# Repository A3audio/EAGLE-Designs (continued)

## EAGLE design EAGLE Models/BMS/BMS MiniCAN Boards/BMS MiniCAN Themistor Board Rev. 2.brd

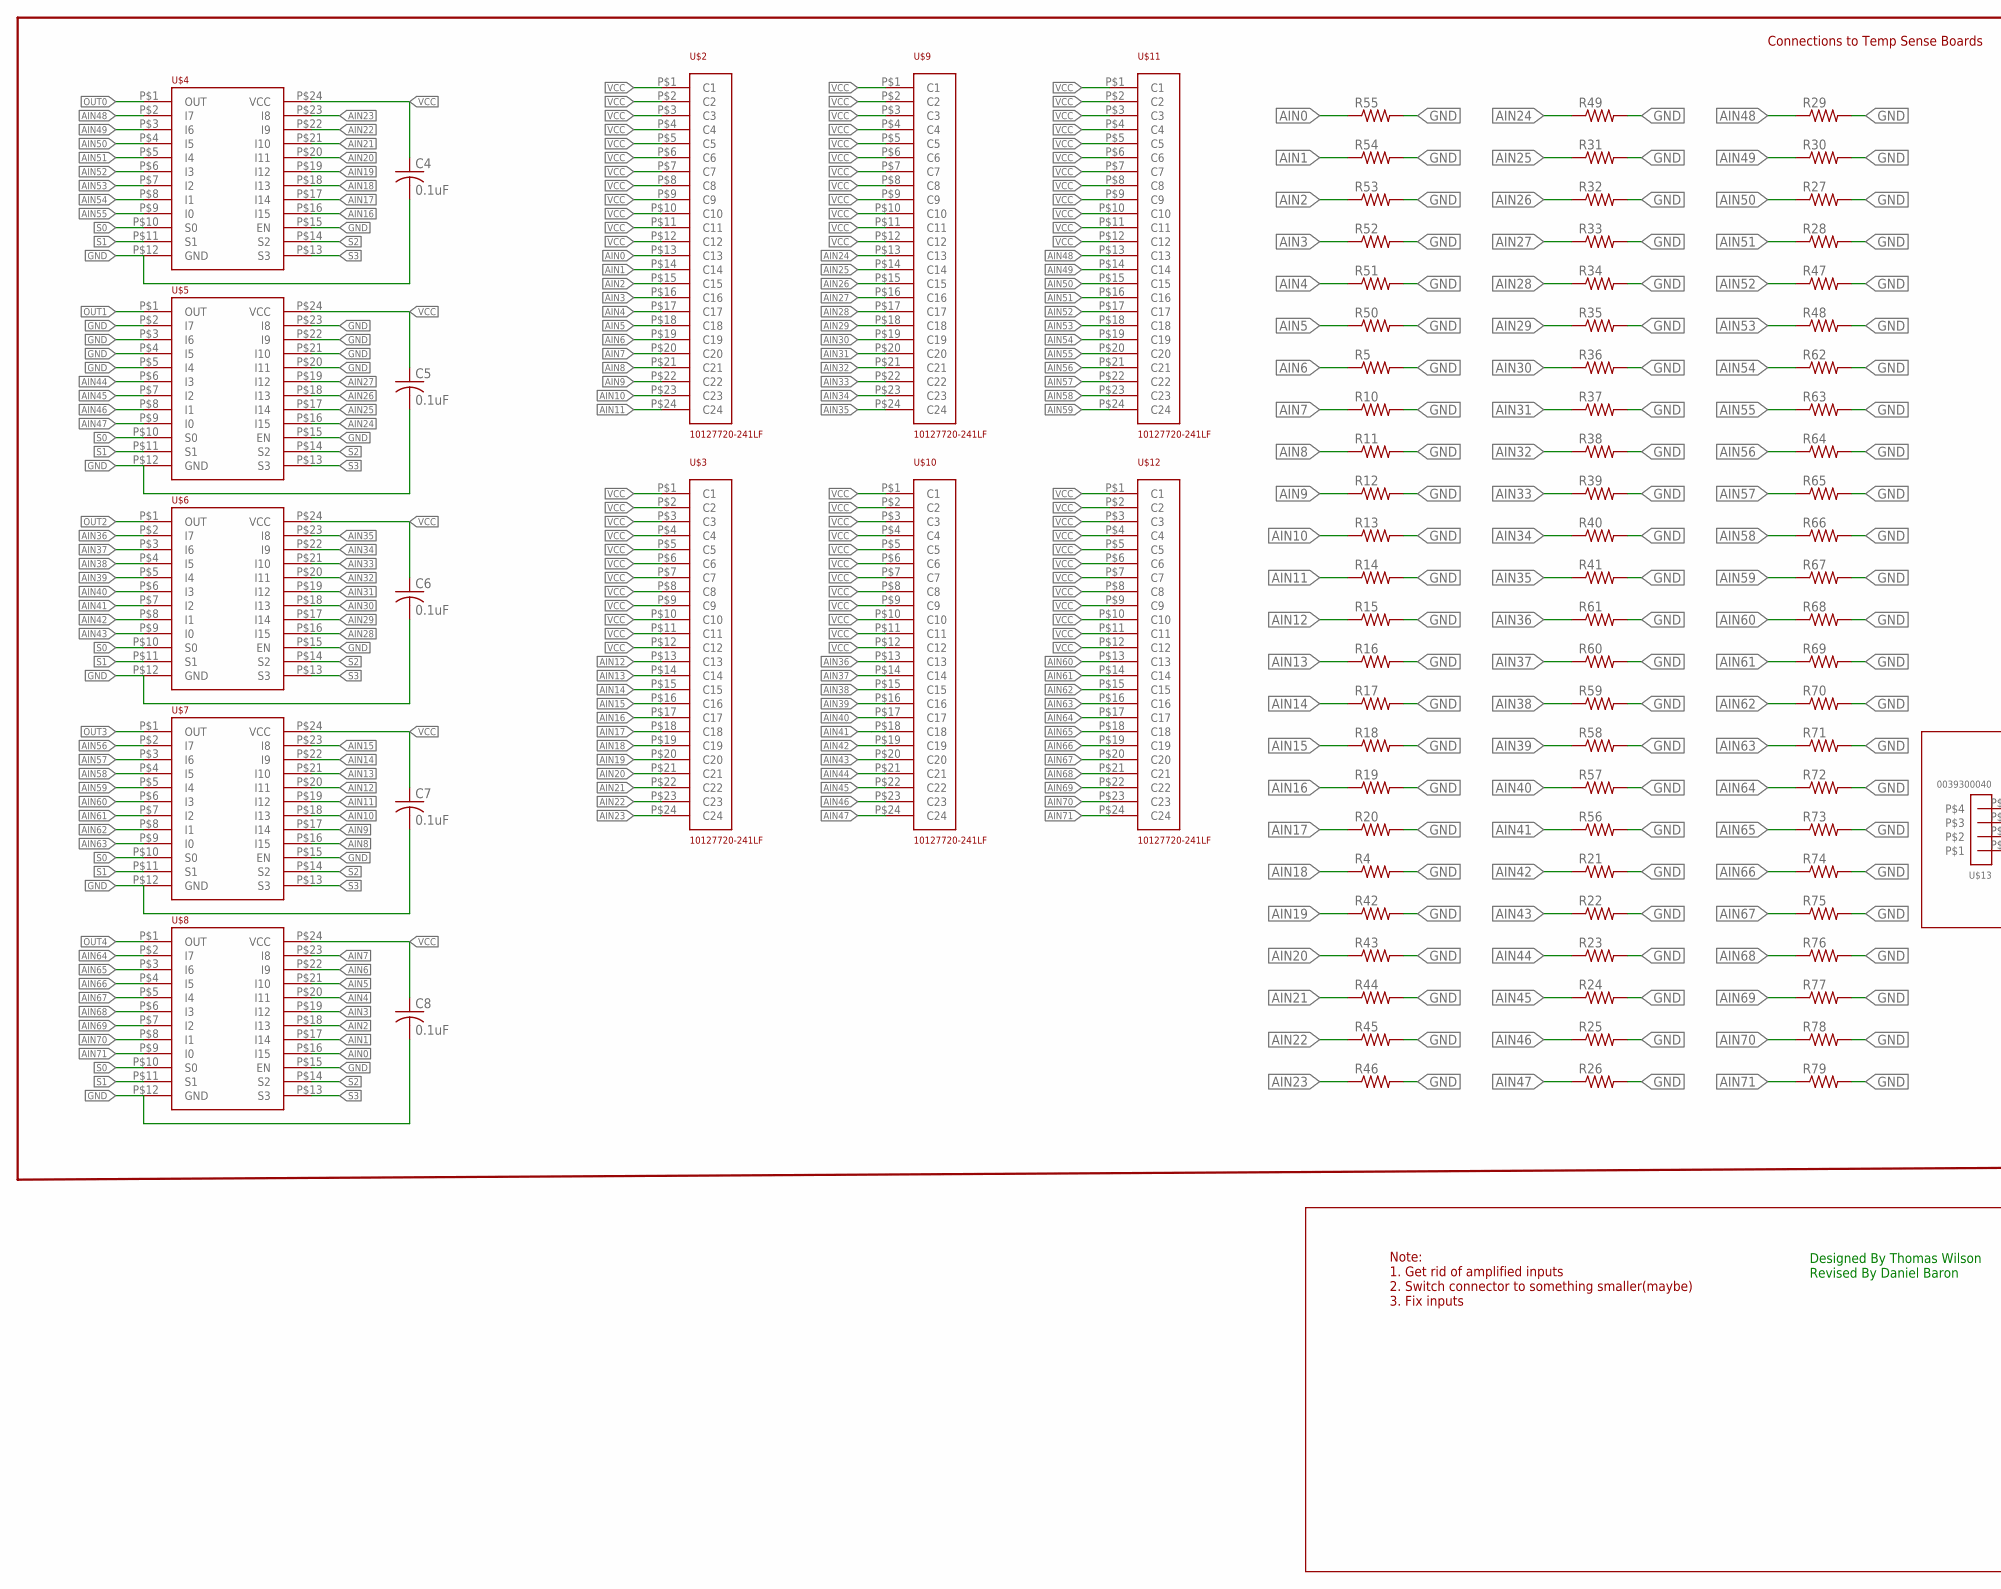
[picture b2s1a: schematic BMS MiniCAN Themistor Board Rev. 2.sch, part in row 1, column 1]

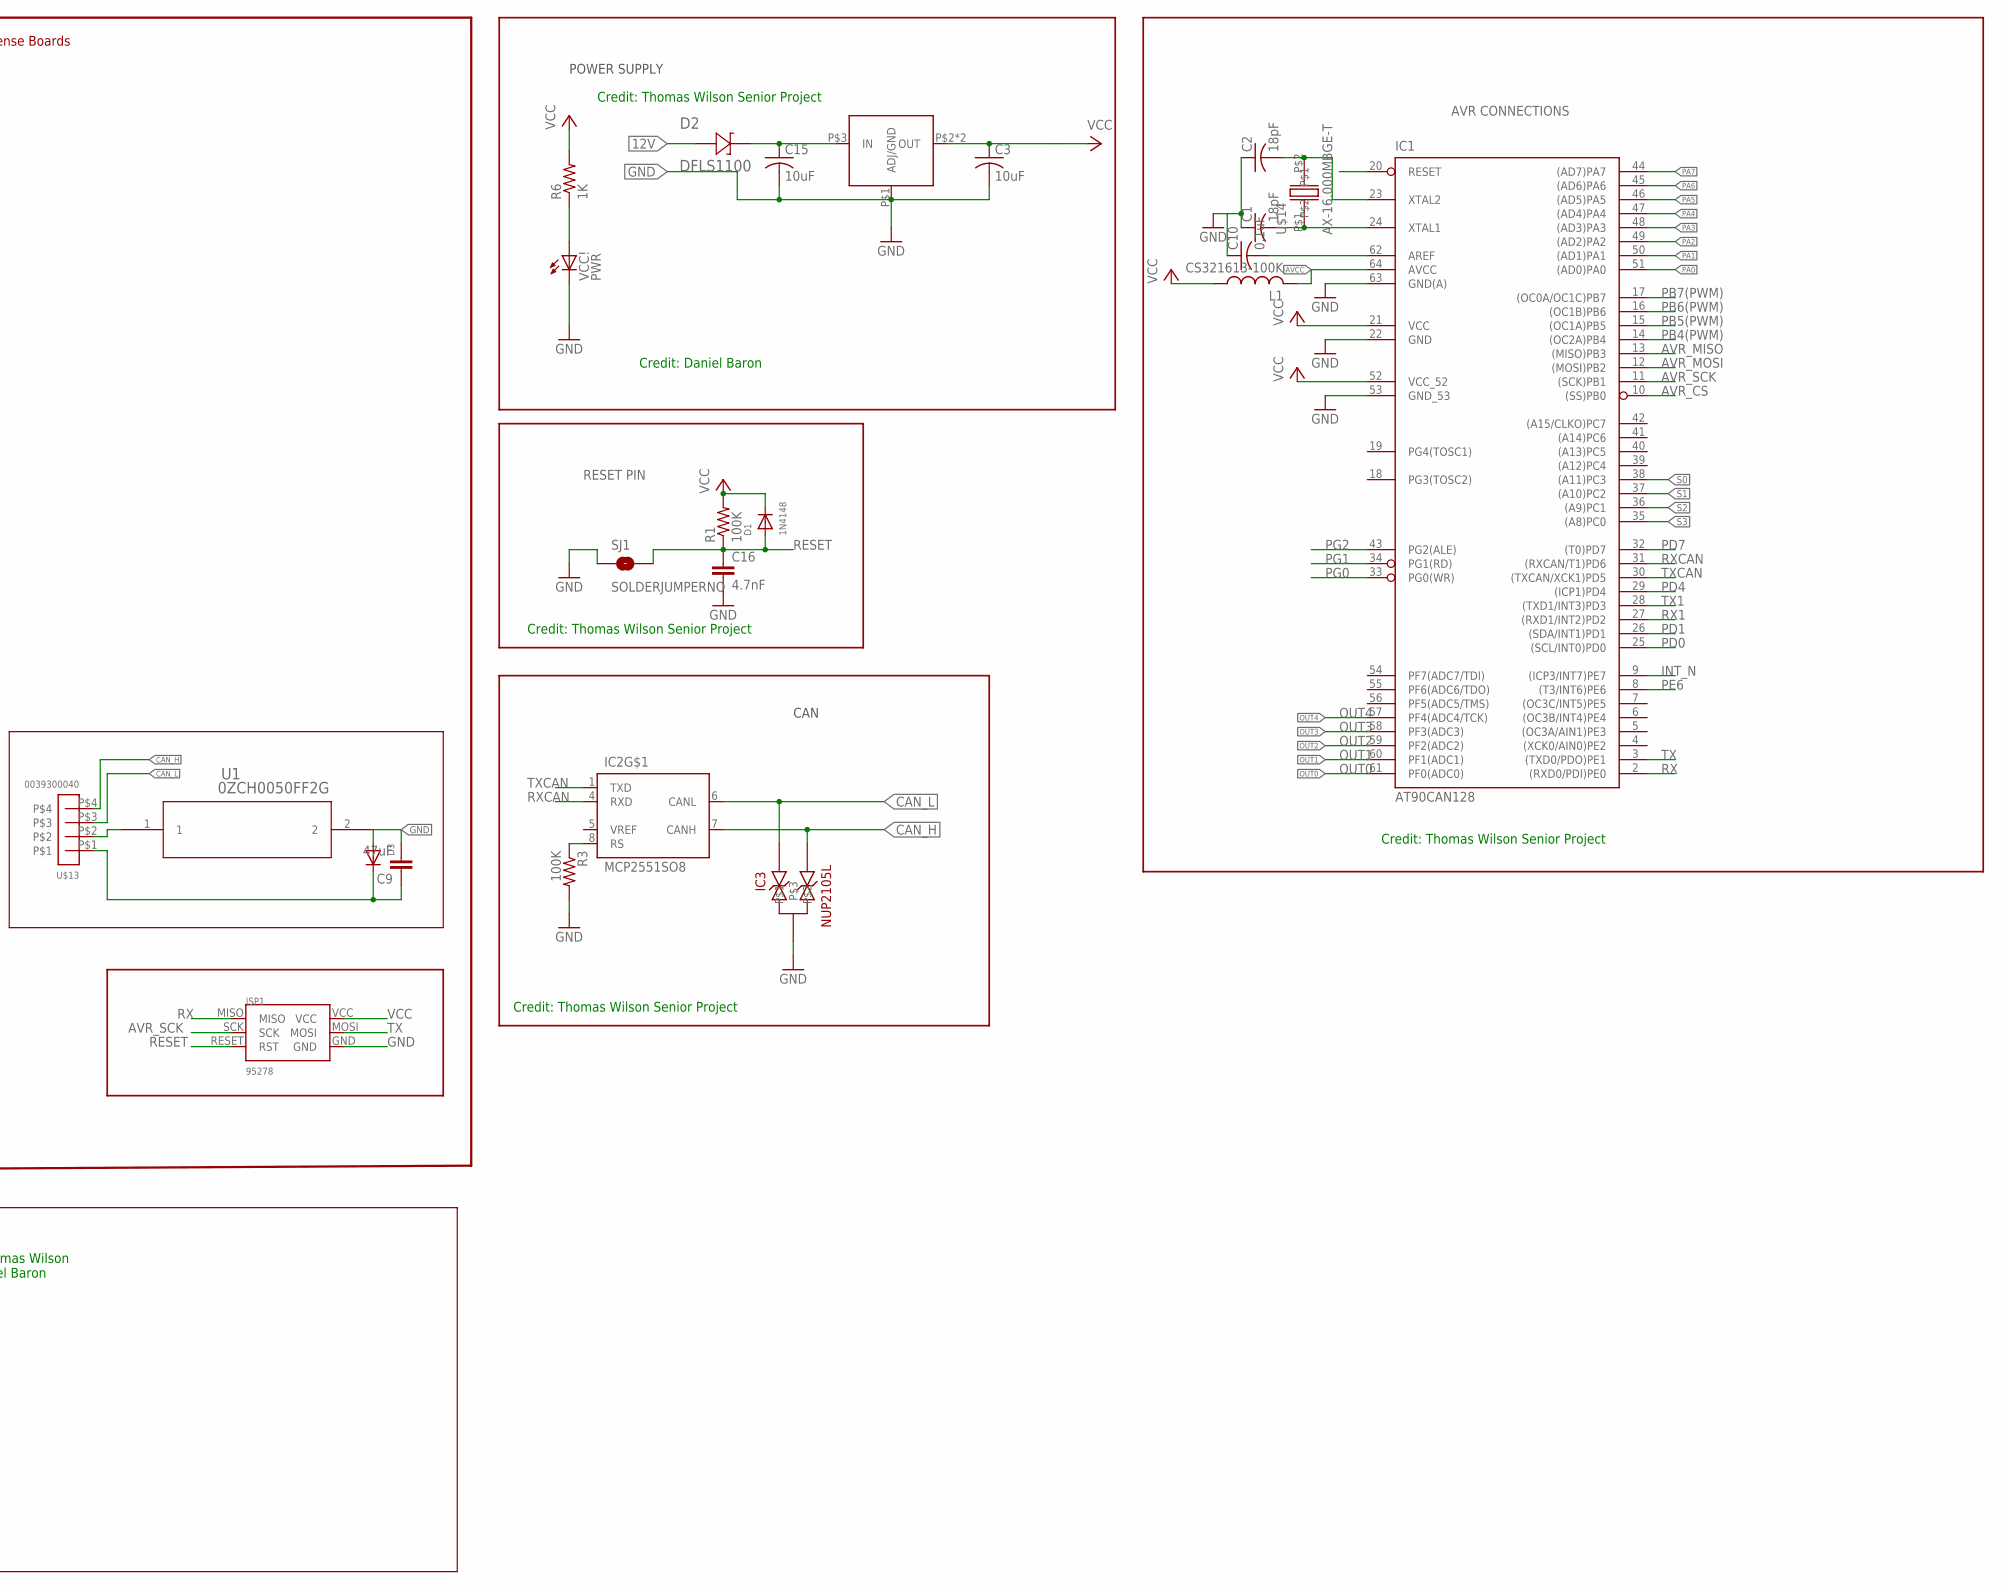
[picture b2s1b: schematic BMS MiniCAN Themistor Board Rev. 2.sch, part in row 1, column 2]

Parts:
C1, C2: 18pF; C0805
C3, C15: 10uF; C0805
C4, C5, C6, C7, C8, C10: 0.1uF; C0805
C9: 47uF; C0805
C16: 4.7nF; 0603-CAP
D1: 1N4148; SOD-123
D2: DFLS1100; POWERDI-123
D3: DIODESOD-323F; SOD-323F
IC1: AT90CAN128; TQFP64
IC2: MCP2551SO8; SO08
IC3: NUP2105L; SOT-23
ISP1: 95278; 6_PIN_.1PITCH
L1: CS321613-100K; L3216C
R1, R3: 100K; R0805
R4, R5, R10, R11, R12, R13, R14, R15, R16, R17, R18, R19, R20, R21, R22, R23, R24, R25, R26, R27, R28, R29, R30, R31, R32, R33, R34, R35, R36, R37, R38, R39, R40, R41, R42, R43, R44, R45, R46, R47, R48, R49, R50, R51, R52, R53, R54, R55, R56, R57, R58, R59, R60, R61, R62, R63, R64, R65, R66, R67, R68, R69, R70, R71, R72, R73, R74, R75, R76, R77, R78, R79: R-US_R0603; R0603
R6: 1K; R0805
SJ1: SOLDERJUMPERNO; SJ_2S-NO
U1: 0ZCH0050FF2G; 0ZCH
U$1: LM117MPX-5.0; SOT223-4
U$2, U$3, U$9, U$10, U$11, U$12: 10127720-241LF
U$4, U$5, U$6, U$7, U$8: CD74HC4067; 24-SOIC
U$13: 0039300040; 4_PIN_MOLEX
U$14: AX-16.000MBGE-T; 2-SMD_NO_LEAD_(DFN_LCC)
VCC!: PWR; CHIPLED_0805

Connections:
12V: C9.1, D2.P$2 (22), D3.C, U$13.P$1
AIN0: R55.1, U$2.P$13 (C13), U$8.P$16 (I15)
AIN1: R54.1, U$2.P$14 (C14), U$8.P$17 (I14)
AIN2: R53.1, U$2.P$15 (C15), U$8.P$18 (I13)
AIN3: R52.1, U$2.P$16 (C16), U$8.P$19 (I12)
AIN4: R51.1, U$2.P$17 (C17), U$8.P$20 (I11)
AIN5: R50.1, U$2.P$18 (C18), U$8.P$21 (I10)
AIN6: R5.1, U$2.P$19 (C19), U$8.P$22 (I9)
AIN7: R10.1, U$2.P$20 (C20), U$8.P$23 (I8)
AIN8: R11.1, U$2.P$21 (C21), U$7.P$16 (I15)
AIN9: R12.1, U$2.P$22 (C22), U$7.P$17 (I14)
AIN10: R13.1, U$2.P$23 (C23), U$7.P$18 (I13)
AIN11: R14.1, U$2.P$24 (C24), U$7.P$19 (I12)
AIN12: R15.1, U$3.P$13 (C13), U$7.P$20 (I11)
AIN13: R16.1, U$3.P$14 (C14), U$7.P$21 (I10)
AIN14: R17.1, U$3.P$15 (C15), U$7.P$22 (I9)
AIN15: R18.1, U$3.P$16 (C16), U$7.P$23 (I8)
AIN16: R19.1, U$3.P$17 (C17), U$4.P$16 (I15)
AIN17: R20.1, U$3.P$18 (C18), U$4.P$17 (I14)
AIN18: R4.1, U$3.P$19 (C19), U$4.P$18 (I13)
AIN19: R42.1, U$3.P$20 (C20), U$4.P$19 (I12)
AIN20: R43.1, U$3.P$21 (C21), U$4.P$20 (I11)
AIN21: R44.1, U$3.P$22 (C22), U$4.P$21 (I10)
AIN22: R45.1, U$3.P$23 (C23), U$4.P$22 (I9)
AIN23: R46.1, U$3.P$24 (C24), U$4.P$23 (I8)
AIN24: R49.1, U$5.P$16 (I15), U$9.P$13 (C13)
AIN25: R31.1, U$5.P$17 (I14), U$9.P$14 (C14)
AIN26: R32.1, U$5.P$18 (I13), U$9.P$15 (C15)
AIN27: R33.1, U$5.P$19 (I12), U$9.P$16 (C16)
AIN28: R34.1, U$6.P$16 (I15), U$9.P$17 (C17)
AIN29: R35.1, U$6.P$17 (I14), U$9.P$18 (C18)
AIN30: R36.1, U$6.P$18 (I13), U$9.P$19 (C19)
AIN31: R37.1, U$6.P$19 (I12), U$9.P$20 (C20)
AIN32: R38.1, U$6.P$20 (I11), U$9.P$21 (C21)
AIN33: R39.1, U$6.P$21 (I10), U$9.P$22 (C22)
AIN34: R40.1, U$6.P$22 (I9), U$9.P$23 (C23)
AIN35: R41.1, U$6.P$23 (I8), U$9.P$24 (C24)
AIN36: R61.1, U$6.P$2 (I7), U$10.P$13 (C13)
AIN37: R60.1, U$6.P$3 (I6), U$10.P$14 (C14)
AIN38: R59.1, U$6.P$4 (I5), U$10.P$15 (C15)
AIN39: R58.1, U$6.P$5 (I4), U$10.P$16 (C16)
AIN40: R57.1, U$6.P$6 (I3), U$10.P$17 (C17)
AIN41: R56.1, U$6.P$7 (I2), U$10.P$18 (C18)
AIN42: R21.1, U$6.P$8 (I1), U$10.P$19 (C19)
AIN43: R22.1, U$6.P$9 (I0), U$10.P$20 (C20)
AIN44: R23.1, U$5.P$6 (I3), U$10.P$21 (C21)
AIN45: R24.1, U$5.P$7 (I2), U$10.P$22 (C22)
AIN46: R25.1, U$5.P$8 (I1), U$10.P$23 (C23)
AIN47: R26.1, U$5.P$9 (I0), U$10.P$24 (C24)
AIN48: R29.1, U$4.P$2 (I7), U$11.P$13 (C13)
AIN49: R30.1, U$4.P$3 (I6), U$11.P$14 (C14)
AIN50: R27.1, U$4.P$4 (I5), U$11.P$15 (C15)
AIN51: R28.1, U$4.P$5 (I4), U$11.P$16 (C16)
AIN52: R47.1, U$4.P$6 (I3), U$11.P$17 (C17)
AIN53: R48.1, U$4.P$7 (I2), U$11.P$18 (C18)
AIN54: R62.1, U$4.P$8 (I1), U$11.P$19 (C19)
AIN55: R63.1, U$4.P$9 (I0), U$11.P$20 (C20)
AIN56: R64.1, U$7.P$2 (I7), U$11.P$21 (C21)
AIN57: R65.1, U$7.P$3 (I6), U$11.P$22 (C22)
AIN58: R66.1, U$7.P$4 (I5), U$11.P$23 (C23)
AIN59: R67.1, U$7.P$5 (I4), U$11.P$24 (C24)
AIN60: R68.1, U$7.P$6 (I3), U$12.P$13 (C13)
AIN61: R69.1, U$7.P$7 (I2), U$12.P$14 (C14)
AIN62: R70.1, U$7.P$8 (I1), U$12.P$15 (C15)
AIN63: R71.1, U$7.P$9 (I0), U$12.P$16 (C16)
AIN64: R72.1, U$8.P$2 (I7), U$12.P$17 (C17)
AIN65: R73.1, U$8.P$3 (I6), U$12.P$18 (C18)
AIN66: R74.1, U$8.P$4 (I5), U$12.P$19 (C19)
AIN67: R75.1, U$8.P$5 (I4), U$12.P$20 (C20)
AIN68: R76.1, U$8.P$6 (I3), U$12.P$21 (C21)
AIN69: R77.1, U$8.P$7 (I2), U$12.P$22 (C22)
AIN70: R78.1, U$8.P$8 (I1), U$12.P$23 (C23)
AIN71: R79.1, U$8.P$9 (I0), U$12.P$24 (C24)
AREF: C10.2, IC1.62 (AREF)
AVCC: IC1.64 (AVCC), L1.2
AVR_CS: IC1.10 ((SS)PB0)
AVR_MISO: IC1.13 ((MISO)PB3)
AVR_MOSI: IC1.12 ((MOSI)PB2)
AVR_SCK: IC1.11 ((SCK)PB1), ISP1.SCK
CAN_H: IC2.7 (CANH), IC3.2, U$13.P$4
CAN_L: IC2.6 (CANL), IC3.1, U$13.P$3
GND: C1.1, C2.1, C3.2, C4.2, C5.2, C6.2, C7.2, C8.2, C9.2, C10.1, C15.2, C16.2, D3.A, IC1.22 (GND), IC1.53 (GND_53), IC1.63 (GND(A)), IC2.2 (GND), IC3.3, ISP1.GND, R3.2, R4.2, R5.2, R10.2, R11.2, R12.2, R13.2, R14.2, R15.2, R16.2, R17.2, R18.2, R19.2, R20.2, R21.2, R22.2, R23.2, R24.2, R25.2, R26.2, R27.2, R28.2, R29.2, R30.2, R31.2, R32.2, R33.2, R34.2, R35.2, R36.2, R37.2, R38.2, R39.2, R40.2, R41.2, R42.2, R43.2, R44.2, R45.2, R46.2, R47.2, R48.2, R49.2, R50.2, R51.2, R52.2, R53.2, R54.2, R55.2, R56.2, R57.2, R58.2, R59.2, R60.2, R61.2, R62.2, R63.2, R64.2, R65.2, R66.2, R67.2, R68.2, R69.2, R70.2, R71.2, R72.2, R73.2, R74.2, R75.2, R76.2, R77.2, R78.2, R79.2, SJ1.1, U1.2, U$1.P$1 (ADJ/GND), U$4.P$12 (GND), U$4.P$15 (EN), U$5.P$2 (I7), U$5.P$3 (I6), U$5.P$4 (I5), U$5.P$5 (I4), U$5.P$12 (GND), U$5.P$15 (EN), U$5.P$20 (I11), U$5.P$21 (I10), U$5.P$22 (I9), U$5.P$23 (I8), U$6.P$12 (GND), U$6.P$15 (EN), U$7.P$12 (GND), U$7.P$15 (EN), U$8.P$12 (GND), U$8.P$15 (EN), VCC!.C
INT_N: IC1.9 ((ICP3/INT7)PE7)
unnamed: C15.1, D2.P$1 (11), U$1.P$3 (IN)
unnamed: IC2.8 (RS), R3.1
unnamed: R6.1, VCC!.A
OUT0: IC1.61 (PF0(ADC0)), U$4.P$1 (OUT)
OUT1: IC1.60 (PF1(ADC1)), U$5.P$1 (OUT)
OUT2: IC1.59 (PF2(ADC2)), U$6.P$1 (OUT)
OUT3: IC1.58 (PF3(ADC3)), U$7.P$1 (OUT)
OUT4: IC1.57 (PF4(ADC4/TCK)), U$8.P$1 (OUT)
PA0: IC1.51 ((AD0)PA0)
PA1: IC1.50 ((AD1)PA1)
PA2: IC1.49 ((AD2)PA2)
PA3: IC1.48 ((AD3)PA3)
PA4: IC1.47 ((AD4)PA4)
PA5: IC1.46 ((AD5)PA5)
PA6: IC1.45 ((AD6)PA6)
PA7: IC1.44 ((AD7)PA7)
PB4(PWM): IC1.14 ((OC2A)PB4)
PB5(PWM): IC1.15 ((OC1A)PB5)
PB6(PWM): IC1.16 ((OC1B)PB6)
PB7(PWM): IC1.17 ((OC0A/OC1C)PB7)
PD0: IC1.25 ((SCL/INT0)PD0)
PD1: IC1.26 ((SDA/INT1)PD1)
PD4: IC1.29 ((ICP1)PD4)
PD7: IC1.32 ((T0)PD7)
PE6: IC1.8 ((T3/INT6)PE6)
PG0: IC1.33 (PG0(WR))
PG1: IC1.34 (PG1(RD))
PG2: IC1.43 (PG2(ALE))
RESET: C16.1, D1.A, IC1.20 (RESET), ISP1.RESET (RST), R1.1, SJ1.2
RX: IC1.2 ((RXD0/PDI)PE0), ISP1.MISO
RX1: IC1.27 ((RXD1/INT2)PD2)
RXCAN: IC1.31 ((RXCAN/T1)PD6), IC2.4 (RXD)
S0: IC1.38 ((A11)PC3), U$4.P$10 (S0), U$5.P$10 (S0), U$6.P$10 (S0), U$7.P$10 (S0), U$8.P$10 (S0)
S1: IC1.37 ((A10)PC2), U$4.P$11 (S1), U$5.P$11 (S1), U$6.P$11 (S1), U$7.P$11 (S1), U$8.P$11 (S1)
S2: IC1.36 ((A9)PC1), U$4.P$14 (S2), U$5.P$14 (S2), U$6.P$14 (S2), U$7.P$14 (S2), U$8.P$14 (S2)
S3: IC1.35 ((A8)PC0), U$4.P$13 (S3), U$5.P$13 (S3), U$6.P$13 (S3), U$7.P$13 (S3), U$8.P$13 (S3)
TX: IC1.3 ((TXD0/PDO)PE1), ISP1.MOSI
TX1: IC1.28 ((TXD1/INT3)PD3)
TXCAN: IC1.30 ((TXCAN/XCK1)PD5), IC2.1 (TXD)
UF_GND: U1.1, U$13.P$2
VCC: C3.1, C4.1, C5.1, C6.1, C7.1, C8.1, D1.C, IC1.21 (VCC), IC1.52 (VCC_52), IC2.3 (VCC), ISP1.VCC, L1.1, R1.2, R6.2, U$1.P$2 (OUT), U$1.P$4 (OUT), U$2.P$1 (C1), U$2.P$2 (C2), U$2.P$3 (C3), U$2.P$4 (C4), U$2.P$5 (C5), U$2.P$6 (C6), U$2.P$7 (C7), U$2.P$8 (C8), U$2.P$9 (C9), U$2.P$10 (C10), U$2.P$11 (C11), U$2.P$12 (C12), U$3.P$1 (C1), U$3.P$2 (C2), U$3.P$3 (C3), U$3.P$4 (C4), U$3.P$5 (C5), U$3.P$6 (C6), U$3.P$7 (C7), U$3.P$8 (C8), U$3.P$9 (C9), U$3.P$10 (C10), U$3.P$11 (C11), U$3.P$12 (C12), U$4.P$24 (VCC), U$5.P$24 (VCC), U$6.P$24 (VCC), U$7.P$24 (VCC), U$8.P$24 (VCC), U$9.P$1 (C1), U$9.P$2 (C2), U$9.P$3 (C3), U$9.P$4 (C4), U$9.P$5 (C5), U$9.P$6 (C6), U$9.P$7 (C7), U$9.P$8 (C8), U$9.P$9 (C9), U$9.P$10 (C10), U$9.P$11 (C11), U$9.P$12 (C12), U$10.P$1 (C1), U$10.P$2 (C2), U$10.P$3 (C3), U$10.P$4 (C4), U$10.P$5 (C5), U$10.P$6 (C6), U$10.P$7 (C7), U$10.P$8 (C8), U$10.P$9 (C9), U$10.P$10 (C10), U$10.P$11 (C11), U$10.P$12 (C12), U$11.P$1 (C1), U$11.P$2 (C2), U$11.P$3 (C3), U$11.P$4 (C4), U$11.P$5 (C5), U$11.P$6 (C6), U$11.P$7 (C7), U$11.P$8 (C8), U$11.P$9 (C9), U$11.P$10 (C10), U$11.P$11 (C11), U$11.P$12 (C12), U$12.P$1 (C1), U$12.P$2 (C2), U$12.P$3 (C3), U$12.P$4 (C4), U$12.P$5 (C5), U$12.P$6 (C6), U$12.P$7 (C7), U$12.P$8 (C8), U$12.P$9 (C9), U$12.P$10 (C10), U$12.P$11 (C11), U$12.P$12 (C12)
XTAL1: C1.2, IC1.24 (XTAL1), U$14.P$1
XTAL2: C2.2, IC1.23 (XTAL2), U$14.P$2

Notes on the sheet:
POWER SUPPLY
CAN
RESET PIN
AVR CONNECTIONS
Credit: Thomas Wilson Senior Project
Designed By Thomas Wilson Revised By Daniel Baron
Credit: Daniel Baron
Note: 1. Get rid of amplified inputs 2. Switch connector to something smaller(maybe) 3. Fix inputs
Connections to Temp Sense Boards

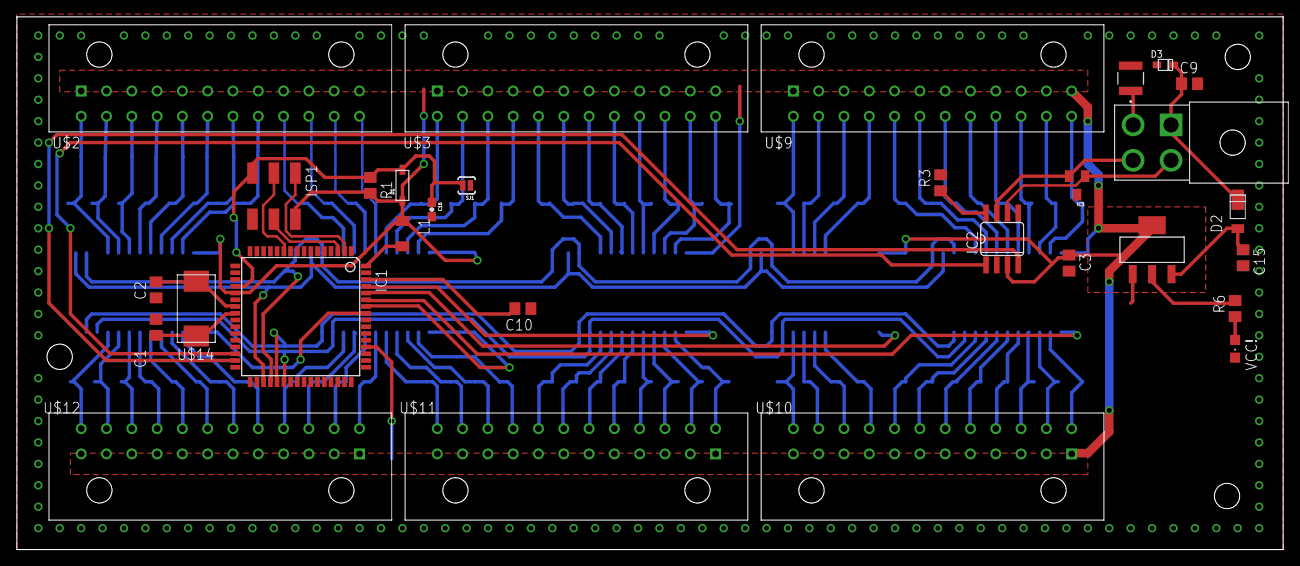
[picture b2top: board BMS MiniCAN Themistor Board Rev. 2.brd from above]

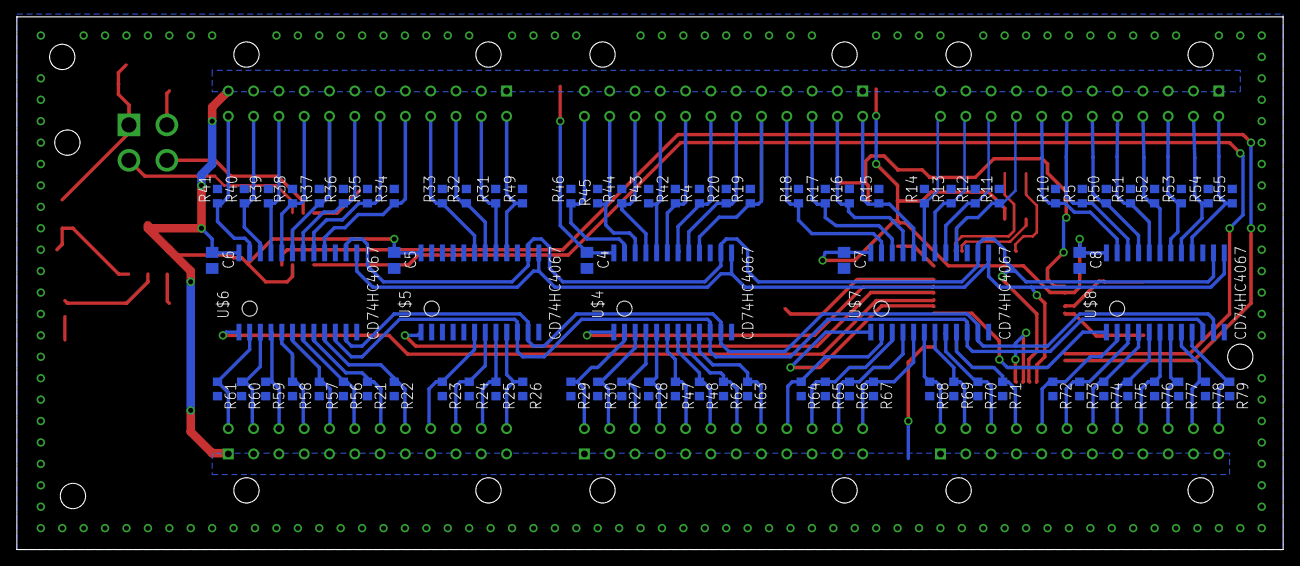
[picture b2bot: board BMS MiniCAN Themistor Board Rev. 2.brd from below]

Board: 2 copper layers, 150.2 x 63.2 mm, 112 parts (82 on the bottom side), 100 nets.

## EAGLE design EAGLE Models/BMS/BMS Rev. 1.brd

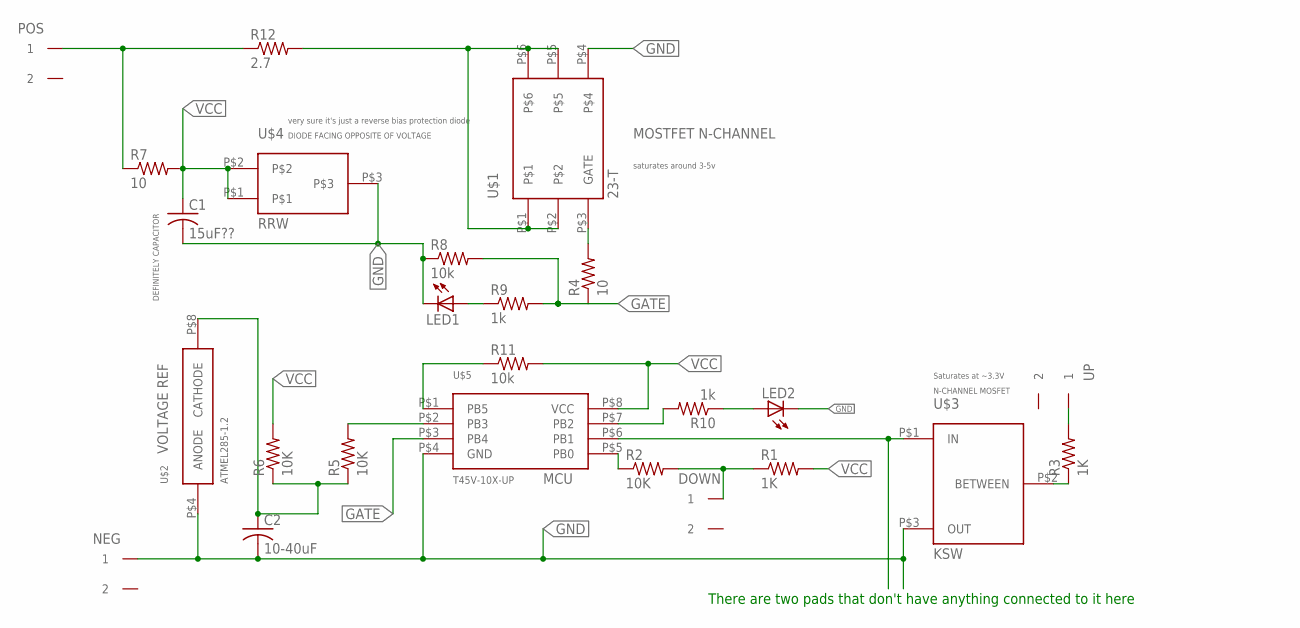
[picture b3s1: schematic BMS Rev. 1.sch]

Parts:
C1: 15uF??; C0805
C2: 10-40uF; C0805
DOWN: CONN_1; CONNECTOR_1
LED1, LED2: LEDCHIPLED_1206; CHIPLED_1206
NEG: CONN_1; CONNECTOR_1
POS: CONN_1; CONNECTOR_1
R1, R3: 1K; R0805
R2, R5, R6: 10K; R0805
R4, R7: 10; R0805
R8, R11: 10k; R0805
R9, R10: 1k; R0805
R12: 2.7; R0805
U$1: 23-T; SOT-23-6
U$2: ATMEL285-1.2; 8-SOIC
U$3: KSW; SOT23-3
U$4: RRW; SOT23-3
U$5: T45V-10X-UP; TSOP-8
UP: CONN_1; CONNECTOR_1

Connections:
DOWN: DOWN.1, R1.1, R2.2
GATE: R4.1, R8.2, R9.2, U$5.P$3 (PB4)
GND: C1.2, C2.2, LED1.C, LED2.C, NEG.1, R8.1, U$1.P$4, U$2.P$4 (ANODE), U$3.P$3 (OUT), U$4.P$3, U$5.P$4 (GND)
unnamed: C2.1, R5.1, R6.1, U$2.P$8 (CATHODE)
unnamed: R10.2, U$5.P$7 (PB2)
unnamed: R4.2, U$1.P$3 (GATE)
unnamed: R3.1, U$3.P$2 (BETWEEN)
unnamed: R11.1, U$5.P$1 (PB5)
unnamed: R2.1, U$5.P$5 (PB0)
unnamed: R5.2, U$5.P$2 (PB3)
unnamed: LED2.A, R10.1
unnamed: R12.2, U$1.P$1, U$1.P$2, U$1.P$5, U$1.P$6
unnamed: LED1.A, R9.1
unnamed: U$3.P$1 (IN), U$5.P$6 (PB1)
POS: POS.1, R7.1, R12.1
UP: R3.2, UP.1
VCC: C1.1, R1.2, R6.2, R7.2, R11.2, U$4.P$1, U$4.P$2, U$5.P$8 (VCC)

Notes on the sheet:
There are two pads that don't have anything connected to it here
VOLTAGE REF
MCU
MOSTFET N-CHANNEL
DIODE FACING OPPOSITE OF VOLTAGE
DEFINITELY CAPACITOR
N-CHANNEL MOSFET
Saturates at ~3.3V
saturates around 3-5v
very sure it's just a reverse bias protection diode

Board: 2 copper layers, 25 parts (0 on the bottom side), 17 nets, no tracks yet.
